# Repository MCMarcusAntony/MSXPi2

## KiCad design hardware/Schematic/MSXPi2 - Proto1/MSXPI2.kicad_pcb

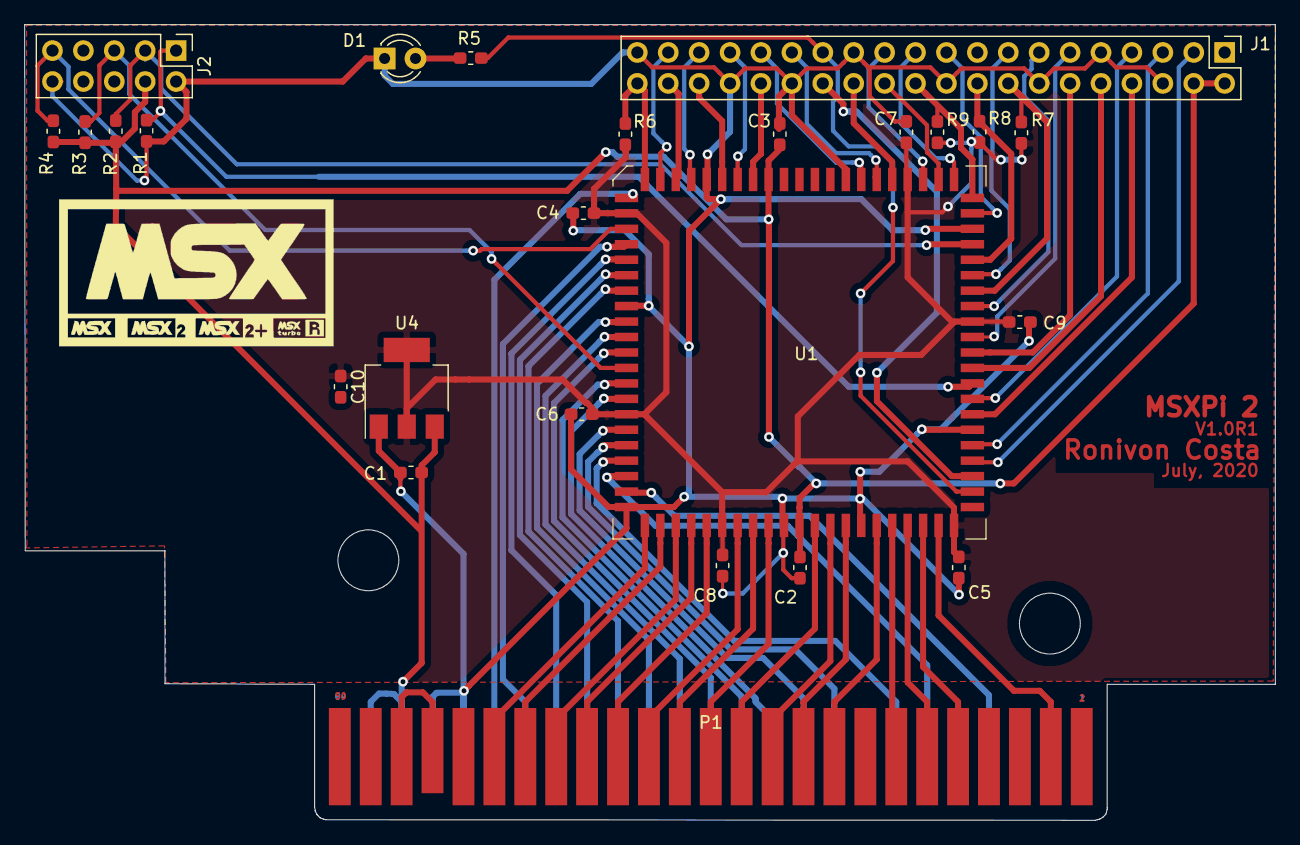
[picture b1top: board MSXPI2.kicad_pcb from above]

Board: 2 copper layers, 102.8 x 65.4 mm, 25 parts (0 on the bottom side), 68 nets.

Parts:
C1, C2, C3, C4, C5, C6, C7, C8, C9, C10: C1; C_0603_1608Metric_Pad1.05x0.95mm_HandSolder
D1: LED; LED_D3.0mm
J1: Raspberry_Pi_2_3; PinHeader_2x20_P2.54mm_Vertical
J2: JTAG; PinHeader_2x05_P2.54mm_Vertical
P1: MSX_CONNECTOR; card_edge_connector
R1, R2, R3, R4, R5, R6, R7, R8, R9: R_US; R_0603_1608Metric_Pad1.05x0.95mm_HandSolder
U1: EPM7128SLC84-15; PLCC-84
U4: LD1117S33TR_SOT223; SOT-223-3_TabPin2

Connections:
+3V3: C4.2, C5.2, C6.2, C7.2, C8.2, C9.2, C10.1, R6.1, R7.1, R8.1, R9.1, U1.13, U1.26, U1.38, U1.53, U1.66, U1.78, U4.2
+5V: C1.1, C2.2, C3.2, J1.2, J1.4, J2.4, P1.45, P1.47, R2.2, R3.2, R4.2, U1.3, U1.43, U4.3
/A0: P1.28, U1.40
/A1: P1.27, U1.21
/A2: P1.30, U1.39
/A3: P1.29, U1.20
/A4: P1.32, U1.37
/A5: P1.31, U1.18
/A6: P1.22, U1.45
/A7: P1.21, U1.25
/A8: P1.24, U1.44
/A9: P1.17, U1.28
/A10: P1.20, U1.46
/A11: P1.19, U1.27
/A12: P1.23, U1.24
/A13: P1.26, U1.41
/A14: P1.25, U1.22
/A15: P1.18, U1.48
/BDIR: P1.10, U1.51
/D0: P1.34, U1.36
/D1: P1.33, U1.17
/D2: P1.36, U1.35
/D3: P1.35, U1.16
/D4: P1.38, U1.34
/D5: P1.37, U1.15
/D6: P1.40, U1.33
/D7: P1.39, U1.12
/IORQ: P1.11, U1.30
/MREQ: P1.12, U1.50
/RD: P1.14, U1.49
/SLTSL: P1.4, U1.52
/WAIT: P1.7, U1.31
/WR: P1.13, U1.29
GNDREF: C1.2, C2.1, C3.1, C4.1, C5.1, C6.1, C7.1, C8.1, C9.1, C10.2, D1.1, J1.6, J1.9, J1.14, J1.20, J1.25, J1.30, J1.34, J1.39, J2.2, J2.10, P1.41, P1.43, R1.1, U1.7, U1.19, U1.32, U1.42, U1.47, U1.59, U1.72, U1.82, U4.1
GPIO0: J1.27, R5.2, U1.55
GPIO1: J1.28, U1.56
GPIO02: J1.3, U1.57
GPIO03: J1.5, U1.58
GPIO04: J1.7, U1.61
GPIO05: J1.29, U1.80
GPIO06: J1.31, U1.81
GPIO07: J1.26, U1.79
GPIO08: J1.24, U1.76
GPIO09: J1.21, U1.75
GPIO10: J1.19, U1.73
GPIO11: J1.23, U1.77
GPIO12: J1.32, U1.4
GPIO13: J1.33, U1.5
GPIO14: J1.8, U1.60
GPIO15: J1.10, U1.63
GPIO16: J1.36, U1.6
GPIO17: J1.11, U1.65
GPIO18: J1.12, U1.64
GPIO19: J1.35, U1.8
GPIO20: J1.38, U1.9
GPIO21: J1.40, R6.2, U1.11
GPIO22: J1.15, U1.69
GPIO23: J1.16, R7.2, U1.68
GPIO24: J1.18, R8.2, U1.70
GPIO25: J1.22, R9.2, U1.74
GPIO26: J1.37, U1.10
GPIO27: J1.13, U1.67
unnamed: D1.2, R5.1
unnamed: P1.44, P1.46
TCK: J2.1, R1.2, U1.62
TDI: J2.9, R4.1, U1.14
TDO: J2.3, R2.1, U1.71
TMS: J2.5, R3.1, U1.23

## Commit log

2020-07-03 initial version, contain only cpld test designs
2020-07-03 cpld pinout configured
2020-07-04 fix to syntar errors
2020-07-05 add bcm pins info to vhd
2020-07-05 build cpld project
2020-07-05 RPi detects writes to 0x8000, but show wrong bus data
2020-07-06 working for port, show corrct Port and Data on RPI
2020-07-06 RPI can see 0x3ff bytes only. Demo working on address 0x10ea
2020-07-06 added msxpi-server to this commit
2020-07-06 write to different mem address below 0x3fff, and io port 0x56
2020-07-06 rom_sim created in the msxpi-server
2020-07-07 write mem/IO, wr/rd/mreq/iorq signals good on RPi
2020-07-07 fix to control signals in msxpi-server
2020-07-07 io read data consistently, but mem read corrupts data
2020-07-24 updated with schematic rev 1
